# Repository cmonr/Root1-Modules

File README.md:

Root1-Modules
=============

Hardware files for Root1 Platform

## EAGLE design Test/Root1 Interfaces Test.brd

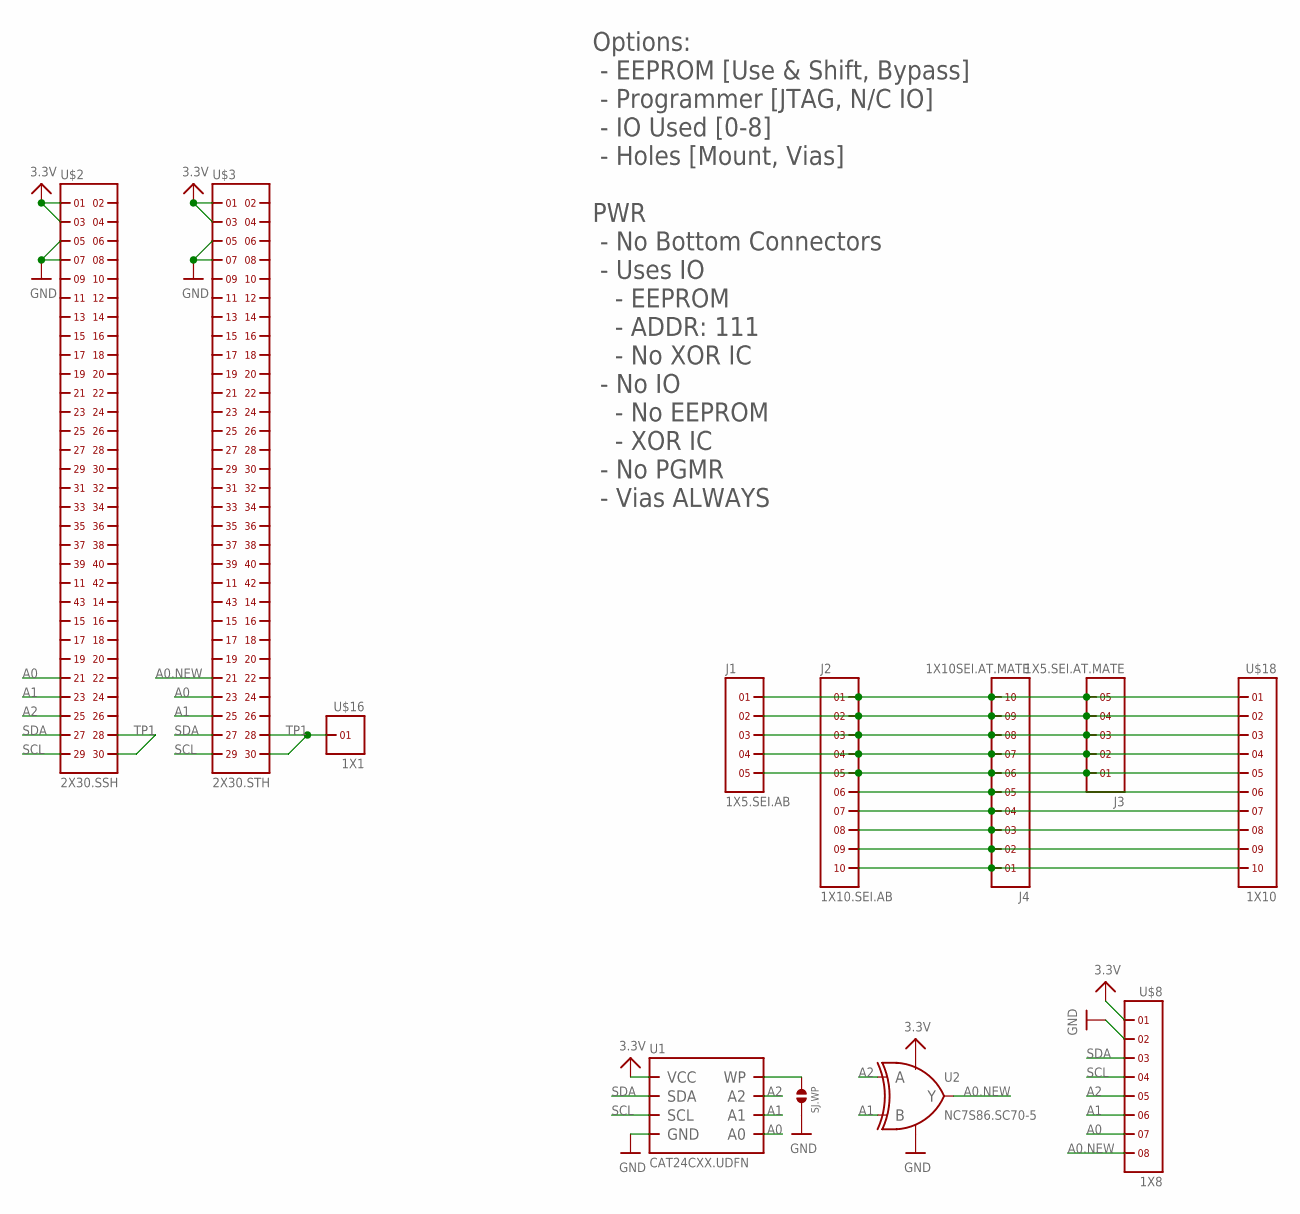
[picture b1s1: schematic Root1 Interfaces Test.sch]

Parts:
J1: 1X5.SEI.AB; SEI-105-02-XX-S-X-AB
J2: 1X10.SEI.AB; SEI-110-02-XX-S-X-AB
J3: 1X5.SEI.AT.MATE; SEI-105-02-XX-S-AT.MATE
J4: 1X10SEI.AT.MATE; SEI-110-02-XX-S-X-AT.MATE
SJ.WP: SOLDERJUMPER.2.MED; 2.MED
U1: CAT24CXX.UDFN; UDFN8.2X3MM
U2: NC7S86.SC70-5; SC70-5
U$2: 2X30.SSH; SSH-030-X.XX-X-D-A
U$3: 2X30.STH; STH-030-X.XX-X-D-A
U$8: 1X8
U$16: 1X1
U$18: 1X10

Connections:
1: J1.1, J2.1, J3.5, J4.10, U$18.1
2: J1.2, J2.2, J3.4, J4.9, U$18.2
3: J1.3, J2.3, J3.3, J4.8, U$18.3
3.3V: U1.8 (VCC), U2.6 (VCC), U$2.1, U$2.3, U$3.1, U$3.3, U$8.1
4: J1.4, J2.4, J3.2, J4.7, U$18.4
5: J1.5, J2.5, J3.1, J4.6, U$18.5
6: J2.6, J4.5, U$18.6
7: J2.7, J4.4, U$18.7
8: J2.8, J4.3, U$18.8
9: J2.9, J4.2, U$18.9
10: J2.10, J4.1, U$18.10
A0: U1.1 (A0), U$2.51, U$3.53, U$8.7
A0.NEW: U2.4 (Y), U$3.51, U$8.8
A1: U1.2 (A1), U2.2 (B), U$2.53, U$3.55, U$8.6
A2: U1.3 (A2), U2.1 (A), U$2.55, U$8.5
GND: SJ.WP.2, U1.4 (GND), U1.PAD (GND), U2.3 (GND), U$2.5, U$2.7, U$3.5, U$3.7, U$8.2
unnamed: SJ.WP.1, U1.7 (WP)
SCL: U1.6 (SCL), U$2.59, U$3.59, U$8.4
SDA: U1.5 (SDA), U$2.57, U$3.57, U$8.3
TP1: U$2.58, U$2.60, U$3.58, U$3.60, U$16.1

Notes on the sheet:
Options: - EEPROM [Use & Shift, Bypass] - Programmer [JTAG, N/C IO] - IO Used [0-8] - Holes [Mount, Vias]
PWR - No Bottom Connectors - Uses IO - EEPROM - ADDR: 111 - No XOR IC - No IO - No EEPROM - XOR IC - No PGMR - Vias ALWAYS

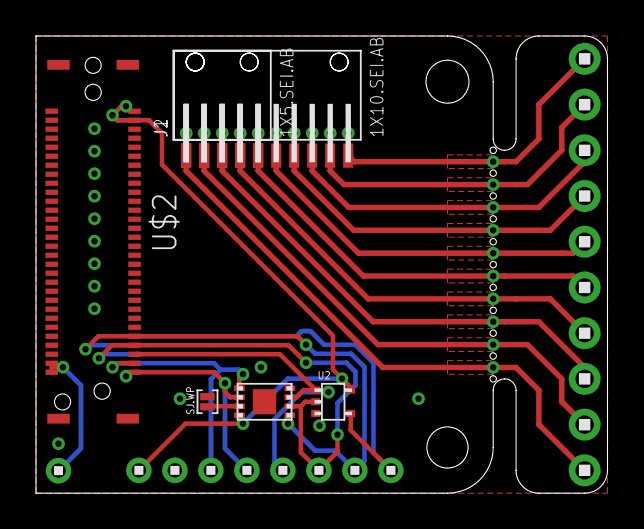
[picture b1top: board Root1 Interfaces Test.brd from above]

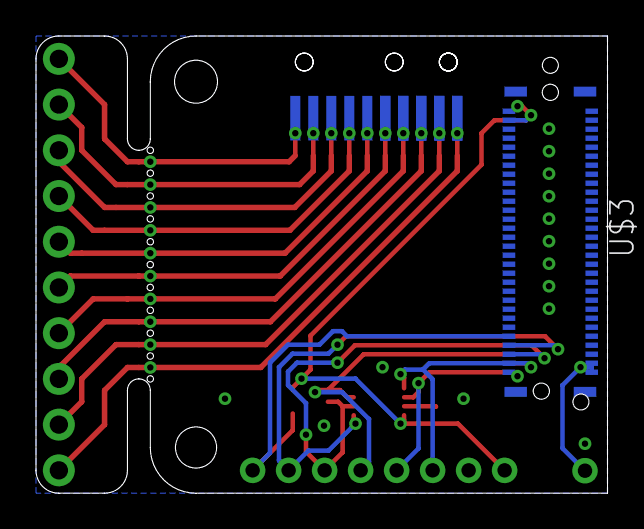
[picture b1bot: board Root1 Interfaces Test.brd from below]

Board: 2 copper layers, 31.8 x 25.4 mm, 12 parts (3 on the bottom side), 20 nets.

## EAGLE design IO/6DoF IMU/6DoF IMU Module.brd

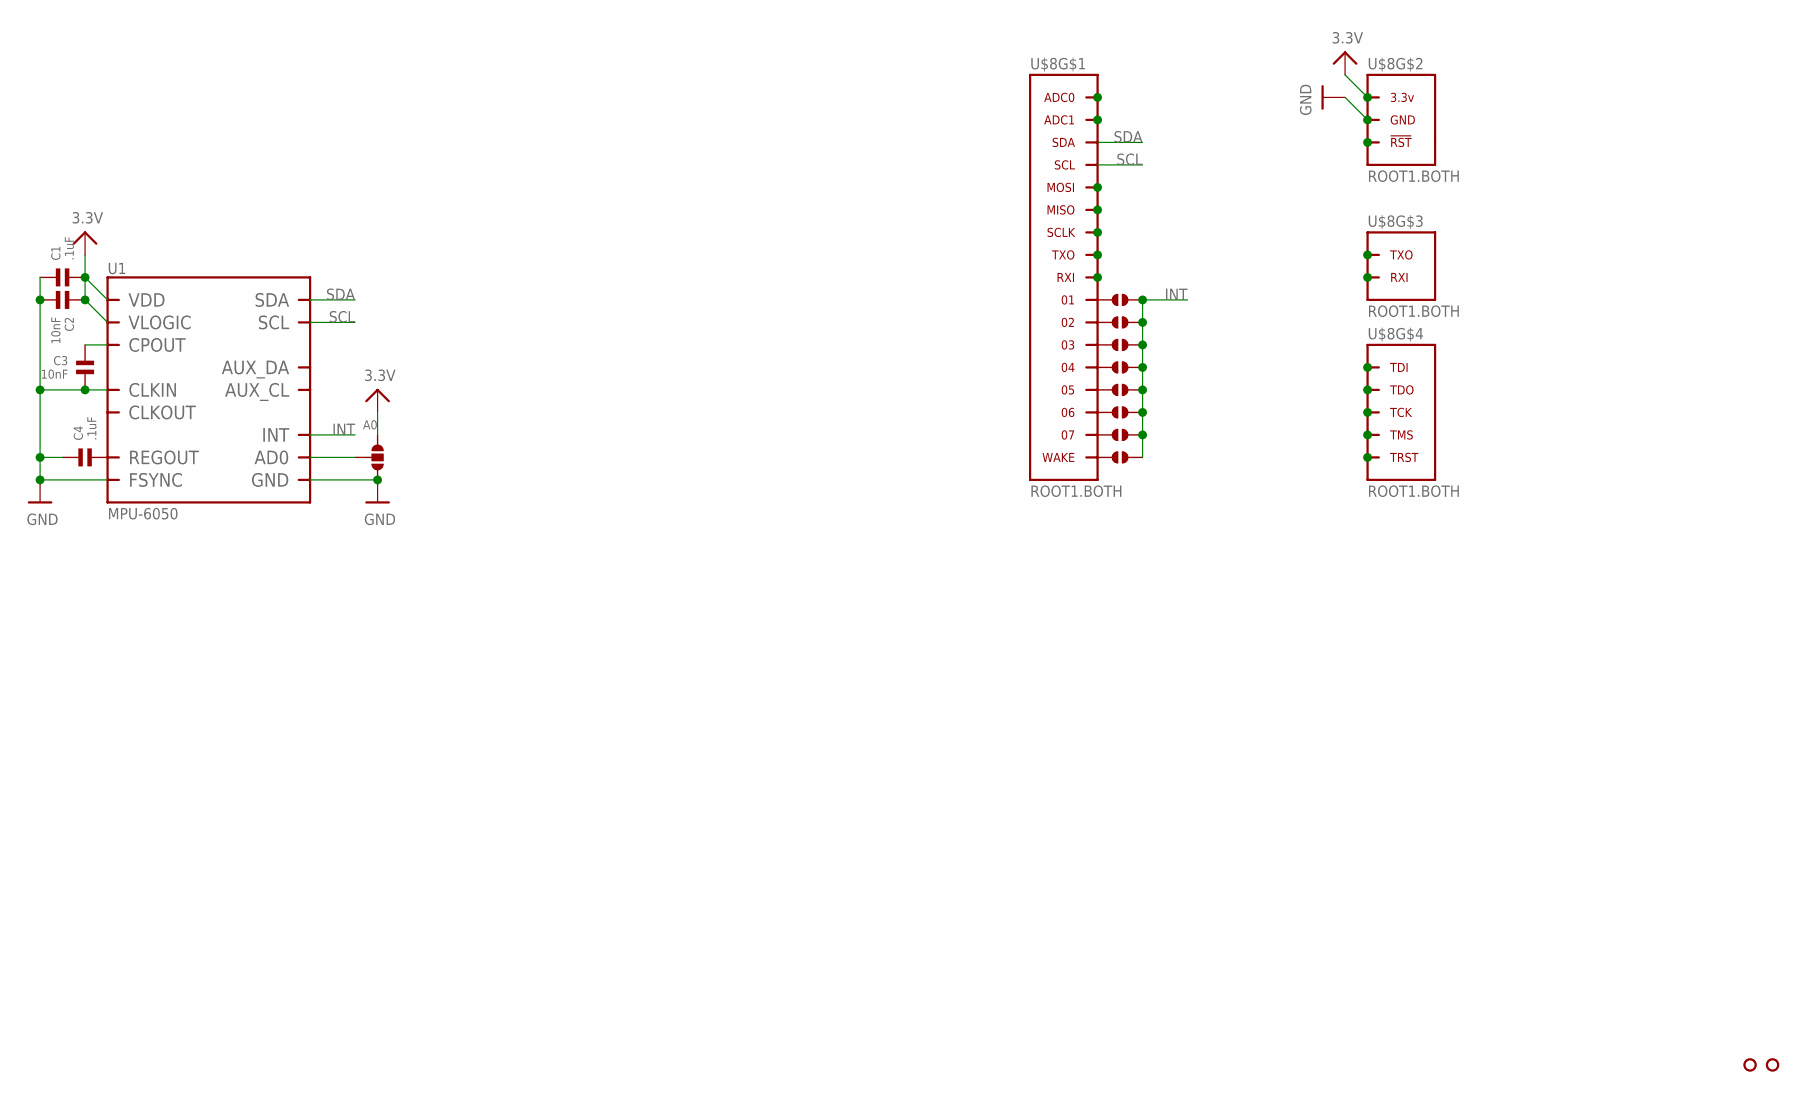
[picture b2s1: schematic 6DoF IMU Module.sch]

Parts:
A0: SOLDERJUMPER.3.MED.23; 3.MED.23
C1, C4: .1uF; 0603
C2, C3: 10nF; 0603
J1, J2, J3, J4, J5, J6, J7, J8: SOLDERJUMPER.2.SML; 2.SML
U1: MPU-6050; QFN.24.4X4
U$4, U$12: HOLE.#2; #2
U$8: ROOT1.BOTH

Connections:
3.3V: A0.1, C1.2, C2.1, U1.8 (VLOGIC), U1.13 (VDD), U$8.3.3V@1 (3.3V), U$8.3.3V@2 (3.3V), U$8.3.3V@3 (3.3V), U$8.3.3V@4 (3.3V), U$8.3.3V@5 (3.3V), U$8.3.3V@6 (3.3V), U$8.3.3V@7 (3.3V), U$8.3.3V@8 (3.3V), U$8.3.3V@9 (3.3V), U$8.3.3V@10 (3.3V), U$8.3.3V@11 (3.3V), U$8.3.3V@12 (3.3V), U$8.3.3V@13 (3.3V), U$8.3.3V@14 (3.3V), U$8.3.3V@15 (3.3V), U$8.3.3V@16 (3.3V), U$8.3.3V@17 (3.3V), U$8.3.3V@18 (3.3V), U$8.3.3V@19 (3.3V), U$8.3.3V@20 (3.3V), U$8.3.3V@21 (3.3V), U$8.3.3V@22 (3.3V), U$8.3.3V@23 (3.3V), U$8.3.3V@24 (3.3V), U$8.3.3V@VIA (3.3V)
GND: A0.3, C1.1, C2.2, C3.2, C4.1, U1.1 (CLKIN), U1.11 (FSYNC), U1.18 (GND), U$8.GND@1 (GND), U$8.GND@2 (GND), U$8.GND@3 (GND), U$8.GND@4 (GND), U$8.GND@5 (GND), U$8.GND@6 (GND), U$8.GND@7 (GND), U$8.GND@8 (GND), U$8.GND@9 (GND), U$8.GND@10 (GND), U$8.GND@11 (GND), U$8.GND@12 (GND), U$8.GND@13 (GND), U$8.GND@14 (GND), U$8.GND@15 (GND), U$8.GND@16 (GND), U$8.GND@17 (GND), U$8.GND@18 (GND), U$8.GND@19 (GND), U$8.GND@20 (GND), U$8.GND@21 (GND), U$8.GND@22 (GND), U$8.GND@23 (GND), U$8.GND@24 (GND), U$8.GND@25 (GND), U$8.GND@26 (GND), U$8.GND@VIA (GND)
INT: J1.2, J2.2, J3.2, J4.2, J5.2, J6.2, J7.2, J8.2, U1.12 (INT)
unnamed: U$8.ADC0, U$8.ADC0@1 (ADC0), U$8.ADC0@VIA (ADC0)
unnamed: U$8.ADC1, U$8.ADC1@1 (ADC1), U$8.ADC1@VIA (ADC1)
unnamed: J1.1, U$8.01, U$8.01@1 (01), U$8.01@VIA (01)
unnamed: U$8.RST (!RST), U$8.RST@1 (!RST), U$8.RST@VIA (!RST)
unnamed: U$8.MOSI, U$8.MOSI@1 (MOSI), U$8.MOSI@VIA (MOSI)
unnamed: U$8.MISO, U$8.MISO@1 (MISO), U$8.MISO@VIA (MISO)
unnamed: U$8.SCLK, U$8.SCLK@1 (SCLK), U$8.SCLK@VIA (SCLK)
unnamed: U$8.TXO.DBG (TXO), U$8.TXO.DBG@1 (TXO), U$8.TXO.DBG@VIA (TXO)
unnamed: U$8.RXI.DBG (RXI), U$8.RXI.DBG@1 (RXI), U$8.RXI.DBG@VIA (RXI)
unnamed: U$8.TDI, U$8.TDI@1 (TDI), U$8.TDI@VIA (TDI)
unnamed: U$8.TDO, U$8.TDO@1 (TDO), U$8.TDO@VIA (TDO)
unnamed: U$8.TCK, U$8.TCK@1 (TCK), U$8.TCK@VIA (TCK)
unnamed: U$8.RXI, U$8.RXI@1 (RXI), U$8.RXI@VIA (RXI)
unnamed: U$8.TXO, U$8.TXO@1 (TXO), U$8.TXO@VIA (TXO)
unnamed: U$8.TMS, U$8.TMS@1 (TMS), U$8.TMS@VIA (TMS)
unnamed: U$8.TRST, U$8.TRST@1 (TRST), U$8.TRST@VIA (TRST)
unnamed: A0.2, U1.9 (AD0)
unnamed: J2.1, U$8.02, U$8.02@1 (02), U$8.02@VIA (02)
unnamed: C4.2, U1.10 (REGOUT)
unnamed: J3.1, U$8.03, U$8.03@1 (03), U$8.03@VIA (03)
unnamed: J4.1, U$8.04, U$8.04@1 (04), U$8.04@VIA (04)
unnamed: J5.1, U$8.05, U$8.05@1 (05), U$8.05@VIA (05)
unnamed: J6.1, U$8.06, U$8.06@1 (06), U$8.06@VIA (06)
unnamed: J7.1, U$8.07, U$8.07@1 (07), U$8.07@VIA (07)
unnamed: J8.1, U$8.WAKE, U$8.WAKE@1 (WAKE), U$8.WAKE@VIA (WAKE)
unnamed: C3.1, U1.20 (CPOUT)
SCL: U1.23 (SCL), U$8.SCL, U$8.SCL@1 (SCL), U$8.SCL@VIA (SCL)
SDA: U1.24 (SDA), U$8.SDA, U$8.SDA@1 (SDA), U$8.SDA@VIA (SDA)

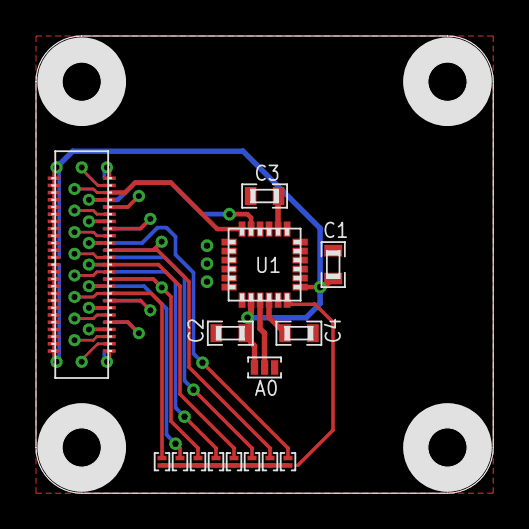
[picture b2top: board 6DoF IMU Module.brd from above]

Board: 2 copper layers, 25.4 x 25.4 mm, 19 parts (0 on the bottom side), 31 nets.

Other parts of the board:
U$2, U$3: HOLE.#2; #2

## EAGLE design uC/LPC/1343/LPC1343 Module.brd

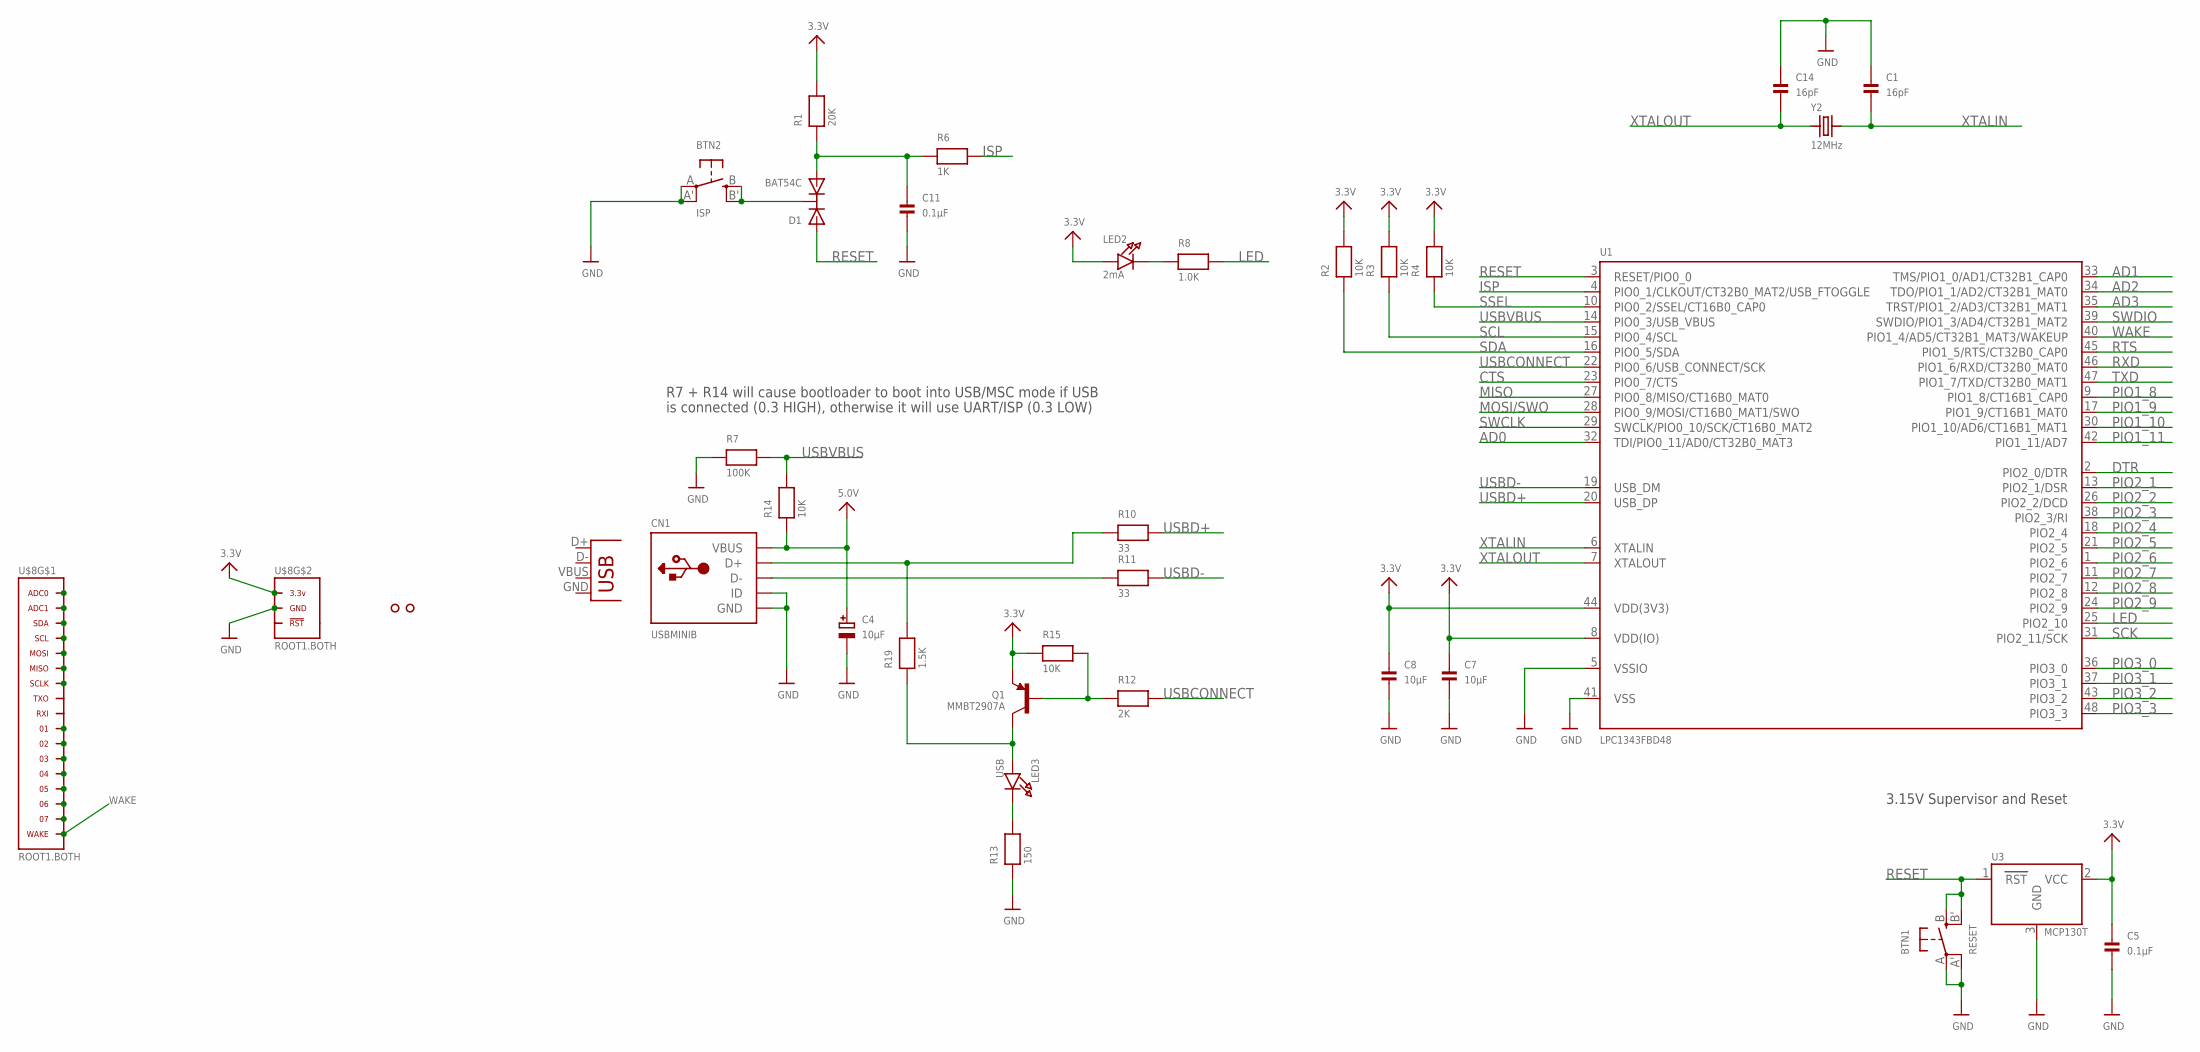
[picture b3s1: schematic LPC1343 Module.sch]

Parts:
BTN1: RESET; EVQ-Q2
BTN2: ISP; EVQ-Q2
C1, C14: 16pF; 0603
C4: 10µF; EIA3216-18/A-R
C5, C11: 0.1µF; 0603
C7, C8: 10µF; 0805
CN1: USBMINIB; USB-MINIB
D1: BAT54C; SOT23-R
LED2: 2mA; CHIPLED_0805
LED3: USB; CHIPLED_0805
Q1: MMBT2907A; SOT23-R
R1: 20K; 0603
R2, R3, R4, R14, R15: 10K; 0603
R6: 1K; 0603
R7: 100K; 0603
R8: 1.0K; 0603
R10, R11: 33; 0603
R12: 2K; 0603
R13: 150; 0603
R19: 1.5K; 0603
U1: LPC1343FBD48; LQFP48
U3: MCP130T; SOT23-R
U$3, U$4: HOLE.2MM; 2MM
U$8: ROOT1.BOTH
X1: USB-MICROB
Y2: 12MHz; CRYSTAL_3.2X2.5

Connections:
3.3V: C5.1, C7.1, C8.1, LED2.A, Q1.2 (E), R1.2, R2.2, R3.2, R4.2, R15.1, U1.8 (VDD(IO)), U1.44 (VDD(3V3)), U3.2 (VCC), U$8.3.3V@1 (3.3V), U$8.3.3V@2 (3.3V), U$8.3.3V@3 (3.3V), U$8.3.3V@4 (3.3V), U$8.3.3V@5 (3.3V), U$8.3.3V@6 (3.3V), U$8.3.3V@7 (3.3V), U$8.3.3V@8 (3.3V), U$8.3.3V@9 (3.3V), U$8.3.3V@10 (3.3V), U$8.3.3V@11 (3.3V), U$8.3.3V@12 (3.3V), U$8.3.3V@13 (3.3V), U$8.3.3V@14 (3.3V), U$8.3.3V@15 (3.3V), U$8.3.3V@16 (3.3V), U$8.3.3V@17 (3.3V), U$8.3.3V@18 (3.3V), U$8.3.3V@19 (3.3V), U$8.3.3V@20 (3.3V), U$8.3.3V@21 (3.3V), U$8.3.3V@22 (3.3V), U$8.3.3V@23 (3.3V), U$8.3.3V@24 (3.3V), U$8.3.3V@VIA (3.3V)
5.0V: C4.+, CN1.VBUS, R14.1
AD0: U1.32 (TDI/PIO0_11/AD0/CT32B0_MAT3)
AD1: U1.33 (TMS/PIO1_0/AD1/CT32B1_CAP0)
AD2: U1.34 (TDO/PIO1_1/AD2/CT32B1_MAT0)
AD3: U1.35 (TRST/PIO1_2/AD3/CT32B1_MAT1)
CTS: U1.23 (PIO0_7/CTS)
DTR: U1.2 (PIO2_0/DTR)
GND: BTN1.A, BTN1.A' (P1), BTN2.A, BTN2.A' (P1), C1.1, C4.-, C5.2, C7.2, C8.2, C11.2, C14.1, CN1.GND, CN1.ID, R7.1, R13.1, U1.5 (VSSIO), U1.41 (VSS), U3.3 (GND), U$8.GND@1 (GND), U$8.GND@2 (GND), U$8.GND@3 (GND), U$8.GND@4 (GND), U$8.GND@5 (GND), U$8.GND@6 (GND), U$8.GND@7 (GND), U$8.GND@8 (GND), U$8.GND@9 (GND), U$8.GND@10 (GND), U$8.GND@11 (GND), U$8.GND@12 (GND), U$8.GND@13 (GND), U$8.GND@14 (GND), U$8.GND@15 (GND), U$8.GND@16 (GND), U$8.GND@17 (GND), U$8.GND@18 (GND), U$8.GND@19 (GND), U$8.GND@20 (GND), U$8.GND@21 (GND), U$8.GND@22 (GND), U$8.GND@23 (GND), U$8.GND@24 (GND), U$8.GND@25 (GND), U$8.GND@26 (GND), U$8.GND@VIA (GND)
ISP: R6.2, U1.4 (PIO0_1/CLKOUT/CT32B0_MAT2/USB_FTOGGLE)
LED: R8.2, U1.25 (PIO2_10)
MISO: U1.27 (PIO0_8/MISO/CT16B0_MAT0)
MOSI/SWO: U1.28 (PIO0_9/MOSI/CT16B0_MAT1/SWO)
unnamed: U$8.ADC0, U$8.ADC0@1 (ADC0), U$8.ADC0@VIA (ADC0)
unnamed: U$8.ADC1, U$8.ADC1@1 (ADC1), U$8.ADC1@VIA (ADC1)
unnamed: U$8.SDA, U$8.SDA@1 (SDA), U$8.SDA@VIA (SDA)
unnamed: U$8.SCL, U$8.SCL@1 (SCL), U$8.SCL@VIA (SCL)
unnamed: U$8.MOSI, U$8.MOSI@1 (MOSI), U$8.MOSI@VIA (MOSI)
unnamed: U$8.MISO, U$8.MISO@1 (MISO), U$8.MISO@VIA (MISO)
unnamed: U$8.SCLK, U$8.SCLK@1 (SCLK), U$8.SCLK@VIA (SCLK)
unnamed: U$8.01, U$8.01@1 (01), U$8.01@VIA (01)
unnamed: U$8.02, U$8.02@1 (02), U$8.02@VIA (02)
unnamed: U$8.03, U$8.03@1 (03), U$8.03@VIA (03)
unnamed: U$8.04, U$8.04@1 (04), U$8.04@VIA (04)
unnamed: U$8.05, U$8.05@1 (05), U$8.05@VIA (05)
unnamed: U$8.06, U$8.06@1 (06), U$8.06@VIA (06)
unnamed: U$8.07, U$8.07@1 (07), U$8.07@VIA (07)
unnamed: LED2.C, R8.1
unnamed: Q1.1 (B), R12.1, R15.2
unnamed: LED3.C, R13.2
unnamed: LED3.A, Q1.3 (C), R19.1
unnamed: CN1.D-, R11.1
unnamed: CN1.D+, R10.1, R19.2
unnamed: BTN2.B (S), BTN2.B' (S1), D1.3 (C)
unnamed: C11.1, D1.2 (A2), R1.1, R6.1
PIO1_8: U1.9 (PIO1_8/CT16B1_CAP0)
PIO1_9: U1.17 (PIO1_9/CT16B1_MAT0)
PIO1_10: U1.30 (PIO1_10/AD6/CT16B1_MAT1)
PIO1_11: U1.42 (PIO1_11/AD7)
PIO2_1: U1.13 (PIO2_1/DSR)
PIO2_2: U1.26 (PIO2_2/DCD)
PIO2_3: U1.38 (PIO2_3/RI)
PIO2_4: U1.18 (PIO2_4)
PIO2_5: U1.21 (PIO2_5)
PIO2_6: U1.1 (PIO2_6)
PIO2_7: U1.11 (PIO2_7)
PIO2_8: U1.12 (PIO2_8)
PIO2_9: U1.24 (PIO2_9)
PIO3_0: U1.36 (PIO3_0)
PIO3_1: U1.37 (PIO3_1)
PIO3_2: U1.43 (PIO3_2)
PIO3_3: U1.48 (PIO3_3)
RESET: BTN1.B (S), BTN1.B' (S1), D1.1 (A1), U1.3 (RESET/PIO0_0), U3.1 (RST)
RTS: U1.45 (PIO1_5/RTS/CT32B0_CAP0)
RXD: U1.46 (PIO1_6/RXD/CT32B0_MAT0)
SCK: U1.31 (PIO2_11/SCK)
SCL: R3.1, U1.15 (PIO0_4/SCL)
SDA: R2.1, U1.16 (PIO0_5/SDA)
SSEL: R4.1, U1.10 (PIO0_2/SSEL/CT16B0_CAP0)
SWCLK: U1.29 (SWCLK/PIO0_10/SCK/CT16B0_MAT2)
SWDIO: U1.39 (SWDIO/PIO1_3/AD4/CT32B1_MAT2)
TXD: U1.47 (PIO1_7/TXD/CT32B0_MAT1)
USBCONNECT: R12.2, U1.22 (PIO0_6/USB_CONNECT/SCK)
USBD+: R10.2, U1.20 (USB_DP)
USBD-: R11.2, U1.19 (USB_DM)
USBVBUS: R7.2, R14.2, U1.14 (PIO0_3/USB_VBUS)
WAKE: U1.40 (PIO1_4/AD5/CT32B1_MAT3/WAKEUP), U$8.WAKE, U$8.WAKE@1 (WAKE), U$8.WAKE@VIA (WAKE)
XTALIN: C1.2, U1.6 (XTALIN), Y2.2
XTALOUT: C14.2, U1.7 (XTALOUT), Y2.1

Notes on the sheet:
3.15V Supervisor and Reset
R7 + R14 will cause bootloader to boot into USB/MSC mode if USB
is connected (0.3 HIGH), otherwise it will use UART/ISP (0.3 LOW)

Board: 2 copper layers, 35 parts (0 on the bottom side), 38 nets, no tracks yet.

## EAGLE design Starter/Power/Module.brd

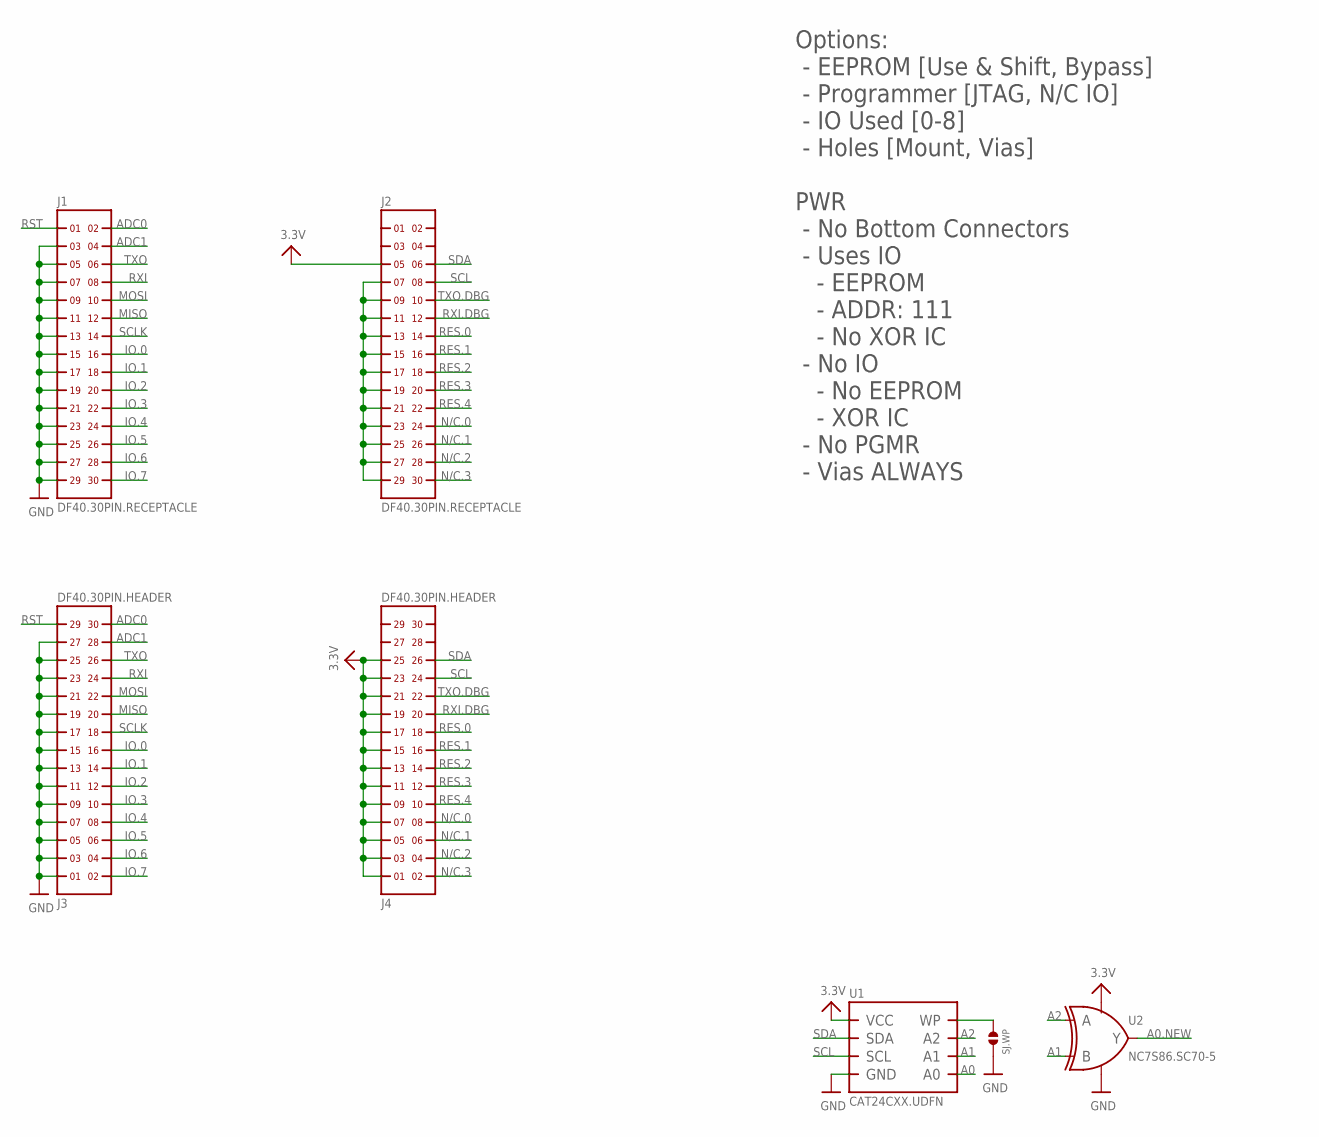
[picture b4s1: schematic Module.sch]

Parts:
J1, J2: DF40.30PIN.RECEPTACLE; DF40(XX)-30DS-0.4V
J3, J4: DF40.30PIN.HEADER; DF40(XX)-30DP-0.4V
SJ.WP: SOLDERJUMPER.2.MED; 2.MED
U1: CAT24CXX.UDFN; UDFN8.2X3MM
U2: NC7S86.SC70-5; SC70-5

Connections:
3.3V: J2.5, J4.1, J4.3, J4.5, J4.7, J4.9, J4.11, J4.13, J4.15, J4.17, J4.19, J4.21, J4.23, J4.25, U1.8 (VCC), U2.6 (VCC)
A0: U1.1 (A0)
A0.NEW: U2.4 (Y)
A1: U1.2 (A1), U2.2 (B)
A2: U1.3 (A2), U2.1 (A)
ADC0: J1.2, J3.30
ADC1: J1.4, J3.28
GND: J1.3, J1.5, J1.7, J1.9, J1.11, J1.13, J1.15, J1.17, J1.19, J1.21, J1.23, J1.25, J1.27, J1.29, J3.1, J3.3, J3.5, J3.7, J3.9, J3.11, J3.13, J3.15, J3.17, J3.19, J3.21, J3.23, J3.25, J3.27, SJ.WP.2, U1.4 (GND), U1.PAD (GND), U2.3 (GND)
IO.0: J1.16, J3.16
IO.1: J1.18, J3.14
IO.2: J1.20, J3.12
IO.3: J1.22, J3.10
IO.4: J1.24, J3.8
IO.5: J1.26, J3.6
IO.6: J1.28, J3.4
IO.7: J1.30, J3.2
MISO: J1.12, J3.20
MOSI: J1.10, J3.22
unnamed: SJ.WP.1, U1.7 (WP)
unnamed: J2.7, J2.9, J2.11, J2.13, J2.15, J2.17, J2.19, J2.21, J2.23, J2.25, J2.27, J2.29
N/C.0: J2.24, J4.8
N/C.1: J2.26, J4.6
N/C.2: J2.28, J4.4
N/C.3: J2.30, J4.2
RES.0: J2.14, J4.18
RES.1: J2.16, J4.16
RES.2: J2.18, J4.14
RES.3: J2.20, J4.12
RES.4: J2.22, J4.10
RST: J1.1
RXI: J1.8, J3.24
RXI.DBG: J2.12, J4.20
SCL: J2.8, J4.24, U1.6 (SCL)
SCLK: J1.14, J3.18
SDA: J2.6, J4.26, U1.5 (SDA)
TXO: J1.6, J3.26
TXO.DBG: J2.10, J4.22

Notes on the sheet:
Options: - EEPROM [Use & Shift, Bypass] - Programmer [JTAG, N/C IO] - IO Used [0-8] - Holes [Mount, Vias]
PWR - No Bottom Connectors - Uses IO - EEPROM - ADDR: 111 - No XOR IC - No IO - No EEPROM - XOR IC - No PGMR - Vias ALWAYS

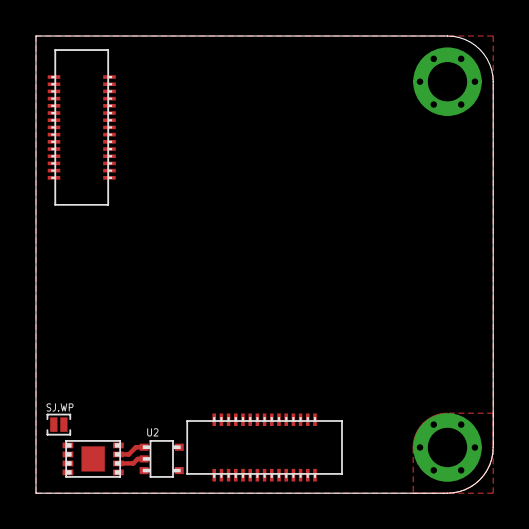
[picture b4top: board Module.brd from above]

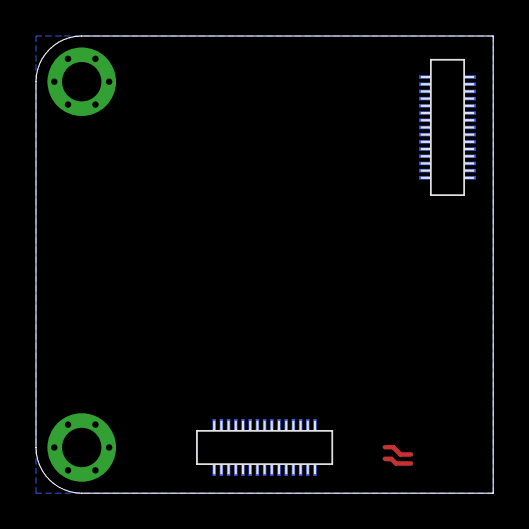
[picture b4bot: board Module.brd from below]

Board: 2 copper layers, 25.4 x 25.4 mm, 7 parts (2 on the bottom side), 34 nets.

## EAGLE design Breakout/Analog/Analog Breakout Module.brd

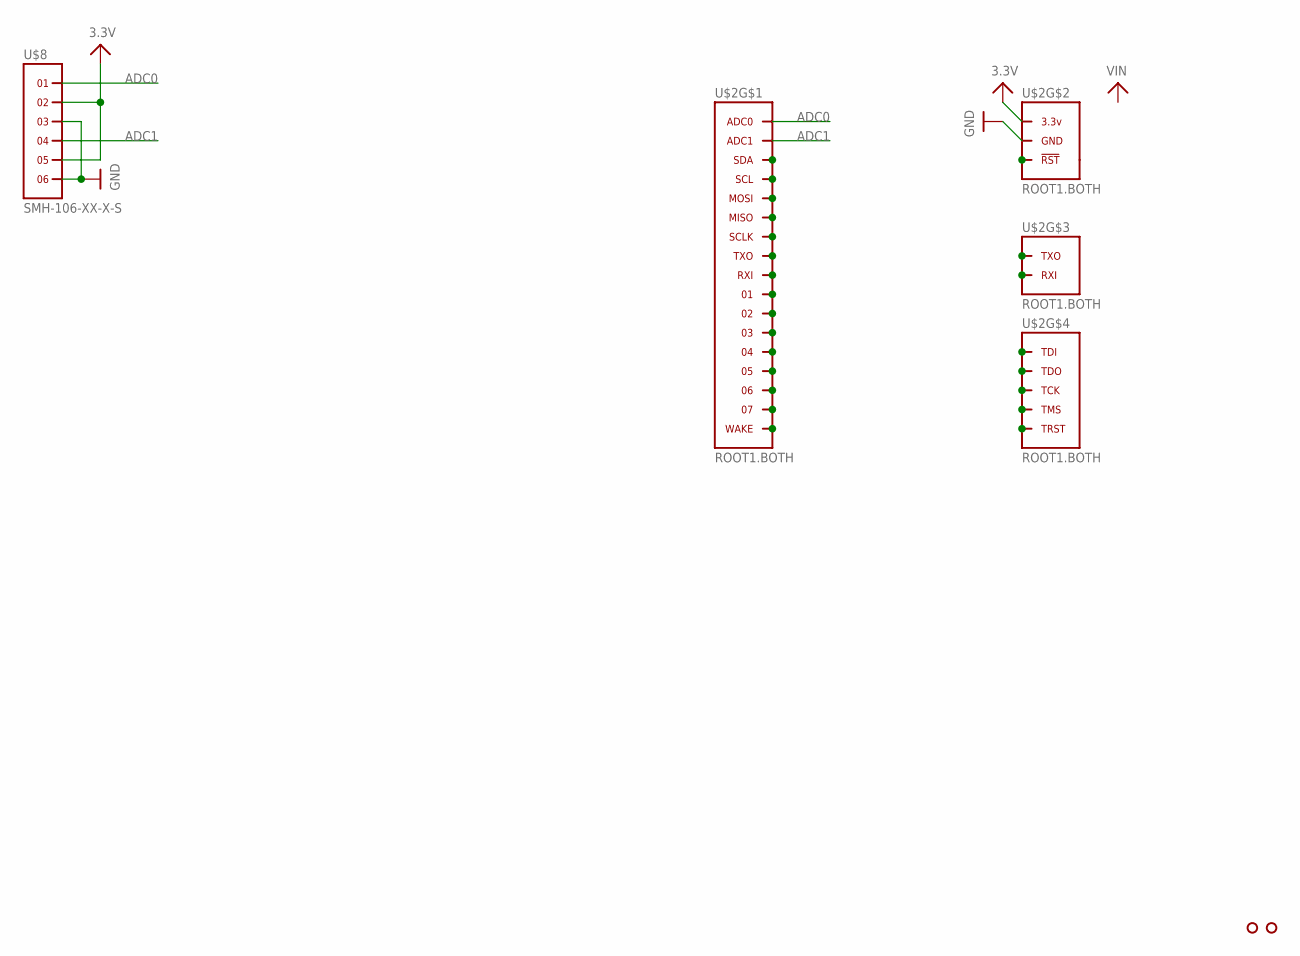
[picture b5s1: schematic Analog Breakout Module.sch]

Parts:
U$2: ROOT1.BOTH
U$3, U$4: HOLE.#2; #2
U$8: SMH-106-XX-X-S

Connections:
3.3V: U$2.3.3V@1 (3.3V), U$2.3.3V@2 (3.3V), U$2.3.3V@3 (3.3V), U$2.3.3V@4 (3.3V), U$2.3.3V@5 (3.3V), U$2.3.3V@6 (3.3V), U$2.3.3V@7 (3.3V), U$2.3.3V@8 (3.3V), U$2.3.3V@9 (3.3V), U$2.3.3V@10 (3.3V), U$2.3.3V@11 (3.3V), U$2.3.3V@12 (3.3V), U$2.3.3V@13 (3.3V), U$2.3.3V@14 (3.3V), U$2.3.3V@15 (3.3V), U$2.3.3V@16 (3.3V), U$2.3.3V@17 (3.3V), U$2.3.3V@18 (3.3V), U$2.3.3V@19 (3.3V), U$2.3.3V@20 (3.3V), U$2.3.3V@21 (3.3V), U$2.3.3V@22 (3.3V), U$2.3.3V@23 (3.3V), U$2.3.3V@24 (3.3V), U$2.3.3V@VIA (3.3V), U$8.2, U$8.5
ADC0: U$2.ADC0, U$2.ADC0@1 (ADC0), U$2.ADC0@VIA (ADC0), U$8.1
ADC1: U$2.ADC1, U$2.ADC1@1 (ADC1), U$2.ADC1@VIA (ADC1), U$8.4
GND: U$2.GND@1 (GND), U$2.GND@2 (GND), U$2.GND@3 (GND), U$2.GND@4 (GND), U$2.GND@5 (GND), U$2.GND@6 (GND), U$2.GND@7 (GND), U$2.GND@8 (GND), U$2.GND@9 (GND), U$2.GND@10 (GND), U$2.GND@11 (GND), U$2.GND@12 (GND), U$2.GND@13 (GND), U$2.GND@14 (GND), U$2.GND@15 (GND), U$2.GND@16 (GND), U$2.GND@17 (GND), U$2.GND@18 (GND), U$2.GND@19 (GND), U$2.GND@20 (GND), U$2.GND@21 (GND), U$2.GND@22 (GND), U$2.GND@23 (GND), U$2.GND@24 (GND), U$2.GND@25 (GND), U$2.GND@26 (GND), U$2.GND@VIA (GND), U$8.3, U$8.6
unnamed: U$2.04, U$2.04@1 (04), U$2.04@VIA (04)
unnamed: U$2.SDA, U$2.SDA@1 (SDA), U$2.SDA@VIA (SDA)
unnamed: U$2.SCL, U$2.SCL@1 (SCL), U$2.SCL@VIA (SCL)
unnamed: U$2.03, U$2.03@1 (03), U$2.03@VIA (03)
unnamed: U$2.MISO, U$2.MISO@1 (MISO), U$2.MISO@VIA (MISO)
unnamed: U$2.SCLK, U$2.SCLK@1 (SCLK), U$2.SCLK@VIA (SCLK)
unnamed: U$2.TXO, U$2.TXO@1 (TXO), U$2.TXO@VIA (TXO)
unnamed: U$2.RXI, U$2.RXI@1 (RXI), U$2.RXI@VIA (RXI)
unnamed: U$2.01, U$2.01@1 (01), U$2.01@VIA (01)
unnamed: U$2.02, U$2.02@1 (02), U$2.02@VIA (02)
unnamed: U$2.MOSI, U$2.MOSI@1 (MOSI), U$2.MOSI@VIA (MOSI)
unnamed: U$2.05, U$2.05@1 (05), U$2.05@VIA (05)
unnamed: U$2.06, U$2.06@1 (06), U$2.06@VIA (06)
unnamed: U$2.07, U$2.07@1 (07), U$2.07@VIA (07)
unnamed: U$2.WAKE, U$2.WAKE@1 (WAKE), U$2.WAKE@VIA (WAKE)
unnamed: U$2.TDI, U$2.TDI@1 (TDI), U$2.TDI@VIA (TDI)
unnamed: U$2.TDO, U$2.TDO@1 (TDO), U$2.TDO@VIA (TDO)
unnamed: U$2.TCK, U$2.TCK@1 (TCK), U$2.TCK@VIA (TCK)
unnamed: U$2.TMS, U$2.TMS@1 (TMS), U$2.TMS@VIA (TMS)
unnamed: U$2.TRST, U$2.TRST@1 (TRST), U$2.TRST@VIA (TRST)
unnamed: U$2.RXI.DBG (RXI), U$2.RXI.DBG@1 (RXI), U$2.RXI.DBG@VIA (RXI)
unnamed: U$2.TXO.DBG (TXO), U$2.TXO.DBG@1 (TXO), U$2.TXO.DBG@VIA (TXO)
unnamed: U$2.RST (!RST), U$2.RST@1 (!RST), U$2.RST@VIA (!RST)

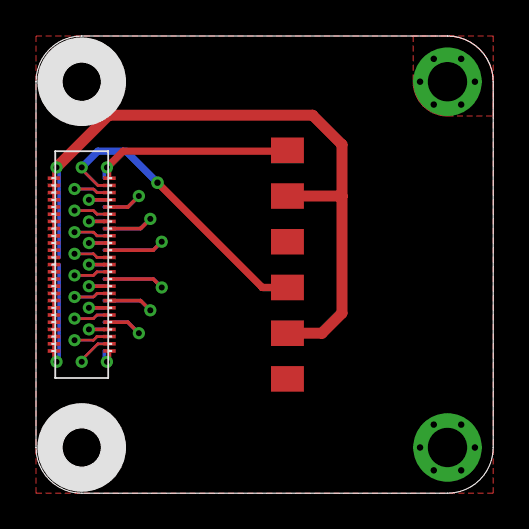
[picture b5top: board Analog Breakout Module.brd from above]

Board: 2 copper layers, 25.4 x 25.4 mm, 4 parts (0 on the bottom side), 27 nets.

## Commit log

2012-08-13 Cloned Root2-Modules .gitignore file
2012-08-13 Root1 CR2032 Power Module: - Initial commit - Working on defining platform header - Hirose DF40.30PIN
2012-08-16 Root1 Starter Module: - Created initial version - Using standard header
2012-08-16 Root1 Dual Motor Module: - Exploring an idea - Sure enough, everything fits!
2012-08-17 Root1 Starter Module: - Updated connectors - Dual sided - Dual #2 screw holes
2012-11-23 Updated Starter Module w/ standard location and new connector spacing
2012-11-23 Simpler Naming format
2012-11-23 Updated Root1 Folder structure
2012-11-23 Added all modules/ideas in progress Finalized Starter Module
2012-11-27 Updated concepts/ideas Renamed 6DoF IMU files Created 6DoF IMU sch and brd (Missing 8-1 smd jumper)
2012-11-27 Began work on 9v Power Module
2012-11-27 Started work on 2xAAA Power Module
2012-11-27 Trying out different connectors
2012-11-27 Added note as to which connectors to use
2012-11-27 Created CR2032 Power Module project.
2012-12-03 Renamed LEDs Module file. Completed Schematic & board layout. Needs silkscreen
2012-12-03 Renamed file to add 'Module' Schematic and Board layout complete. Needs completed Silkscreen
2012-12-03 Renamed file to MicroSD Module. Completed Schematic and Board Layout. Needs silkscreen.
2012-12-03 Renamed file Hex Motor Module. Completed Schematic. Board layout and silkscreen needed.
2012-12-03 Updated silkscreen for 6DoF Module.
2012-12-03 Created Bluetooth [RN-41] Module Schematic and Layout. Still needs Pull-Down resistors w/ SMD Pads, Connected/Status leds, silkscreen, and Factory Reset button.
2012-12-03 Updated Polygon rank of GND signals (1->6)
2012-12-03 Ignore .bak files
2012-12-03 Created Breakouts for Horizontal and Vertical connectors.
2012-12-03 Updated Root1 connector labels. Renamed Dual Horizontal Breakout Module. Both breakout files need silkscreen.
2013-01-23 Renamed to Lipo Module
2013-01-23 Renamed Dual Vertical to Breadboard Breakout Module
2013-01-23 Cleaned up Quad Motor directory
2013-01-23 Completed uSD Module
2013-01-23 Completed 16 PWM LEDs Module
2013-01-23 Completed 6DoF IMU (MPU6050) Module
2013-01-23 Completed Bluetooth (RN-41) Module
2013-01-23 Renamed Bluetooth files for consistency
2013-01-23 Adding unversioned Bluetooth files
2013-01-23 Completed LM3S811 uC Module
2013-01-23 Moved LM3S811 into LM3S/811 directory
2013-01-23 Completed MSP430G2432 uC Module
2013-01-24 Updated Starter Module with standard silkscreen and included all libraries.
2013-01-24 Renamed files to allow for easier renaming in the future (it makes sense, I swear...)
2013-01-24 Created FM Transceiver Module using SI4721 Schematic needs TPA6111, jumpers, and I2C/SPI mapping
2013-01-24 Updated starter files for XBee, Nordic, and Bluetooth LE Modules
2013-01-24 Updated starter files for 16x Servo, Console, and Robot Systems
2013-01-24 Renamed Breadboard Breakout Module to Horizontal Breakout Module
2013-01-24 Created Vertical Breakout Module
2013-01-24 Removed 3 Axis Accelerometer, Gyro, and Magnetometer Modules... for now.
2013-01-24 Reverted EEPROM to Starter file
2013-01-24 Updated Starter Files for Display and Capacitive Modules
2013-01-24 Created Debug Module
2013-01-24 Renamed Quad Motor Module to Dual Motor Module
2013-01-24 Extracted core of LPC1343 required circuitry and began LPC1343 uC Module
2013-01-24 Moved LPC1343 MOdule to LPC/1343/
2013-01-24 Updated Root1 header on LPC1343 MOdule
2013-01-24 Began Universal Debugger Module Idea inspired/based off of Dangerous Prototype's Bus Blaster
2013-01-24 Removed .bak file
2013-01-25 Completed schematic for FM Transceiver (SI4721) Layout completed. Routing needed...
2013-01-25 Updated starter module to updated website (AnomalousMaker.com)
2013-01-25 Updated starter file for Vertical Breakout
2013-01-26 Completed FM Transceiver Module
2013-01-26 Tweaked bottom silkscreen and added more GND Plane space
2013-01-27 Fixed size of version number on bottom silkscreen
2013-01-28 Updated silkscreen on Debug Module
2013-01-28 Completed Debug Module Added/began Thermocouple Module
2013-01-29 Completed Thermocouple Module
2013-01-29 Renamed folder to Thermocouple
2013-02-05 16 PWM LEDs Module: -Change package of C2
2013-02-05 Created and completed the Random Bit Module
2013-03-16 Created Dual Motor Module. Schematic complete, components laid out, routing still needed.
2013-03-16 Updated Starter Module for updated holes, support for external power, and updated header from library.
2013-03-16 Added .dxf to .gitignore
2013-03-16 Added structural Vias to Vin and GND Vias
2013-03-17 Created and completed Vertical Breakout Module
2013-03-17 Created and completed IO Breakout Module
2013-03-17 Created and completed Serial Breakout Module
2013-03-17 Completed Vertical Breakout Module
2013-03-17 Updated silkscreen on Dual Motor Module
2013-03-17 Created and completed Quad Mosfet Module
2013-03-18 Created and completed Vin Buck Pwr Module
2013-03-18 Created and completed PCB USB Pwr Module
2013-03-18 Created and completed Dual Servo Module
2013-03-19 Created and completed Edge Touch Module
2013-03-19 Created and completed Analog Breakout Module
2013-03-20 Created and completed 9DoF IMU Module
2013-03-20 Renamed 6DoF IMU (MPU6050) Module to 6DoF IMU Module
2013-03-20 Renamed 6DoF IMU Module folder to match directory structure
2013-03-20 Updated 6DoF IMU Module silkscreen and connections.
2013-03-20 Updated silkscreen on 9DoF IMU Module
2013-05-26 Investigating idea to get rid of solder jumpers. Using LoKi Plank scheme of EEPROM and LFSF to auto-assign pins. Also moving to using two connectors instead of one for conector integrety nd module st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
2013-05-28 Working on Eagle "parts" for new Root1 scheme
2013-05-29 Autogenerated preview images for PCBs and schematics. Also, because Eagle likes to save the version number in the .brd files, some of them got updates as well...
2013-05-29 More work on new headers. Focusing on H1, and it's various IO schemes.
2013-08-05 Created Test Module to test out Samtec SSH, STH, and SEI headers, along with EEPROM/Loki Scheme, and breakable PCB idea.
2013-08-13 Fixed routing issue in Root1 Interface Test PCB. EEPROM Address did not autoincrement...
2013-10-07 Modified Root1 Test PCB for a simplified pin scheme Module config parts (EEPRON & XOR) have been laid out and routed

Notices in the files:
parts and their libraries:
microbuilder: This work is placed in the public domain, and may be freely used for commercial and non-commercial work with the following conditions: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
SparkFun: Licensing: CC v3.0 Share-Alike You are welcome to use this library for commercial purposes.
